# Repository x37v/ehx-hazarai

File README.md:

EHX stereo memory man with HAZARAI mod board
========

Kicad project, schematic and board

Inputs: beat/gate [filtered or unfiltered]
Outputs: loop, beat

Resources
---
* [Electro-Harmonix Stereo Memory Man with Hazarai](http://www.ehx.com/products/stereo-memory-man-with-hazarai) product page
* [dancerobotdance modified Stereo Memory Man with Hazarai](http://dancerobotdance.com/2011/05/modified-ehx-stereo-memory-man/) blog entry
* [navs.modular.lab More Hazarai! EHX SMMH Modification](http://navsmodularlab.blogspot.com/2009/08/more-hazarai-ehx-smmh-modification.html) blog entry
* [navs.modular.lab Even More Hazarai!](http://navsmodularlab.blogspot.com/2011/10/even-more-hazarai.html) blog entry
* [transistor cookbook](http://www.nutsvolts.com/magazine/article/bipolar_transistor_cookbook_part_3)

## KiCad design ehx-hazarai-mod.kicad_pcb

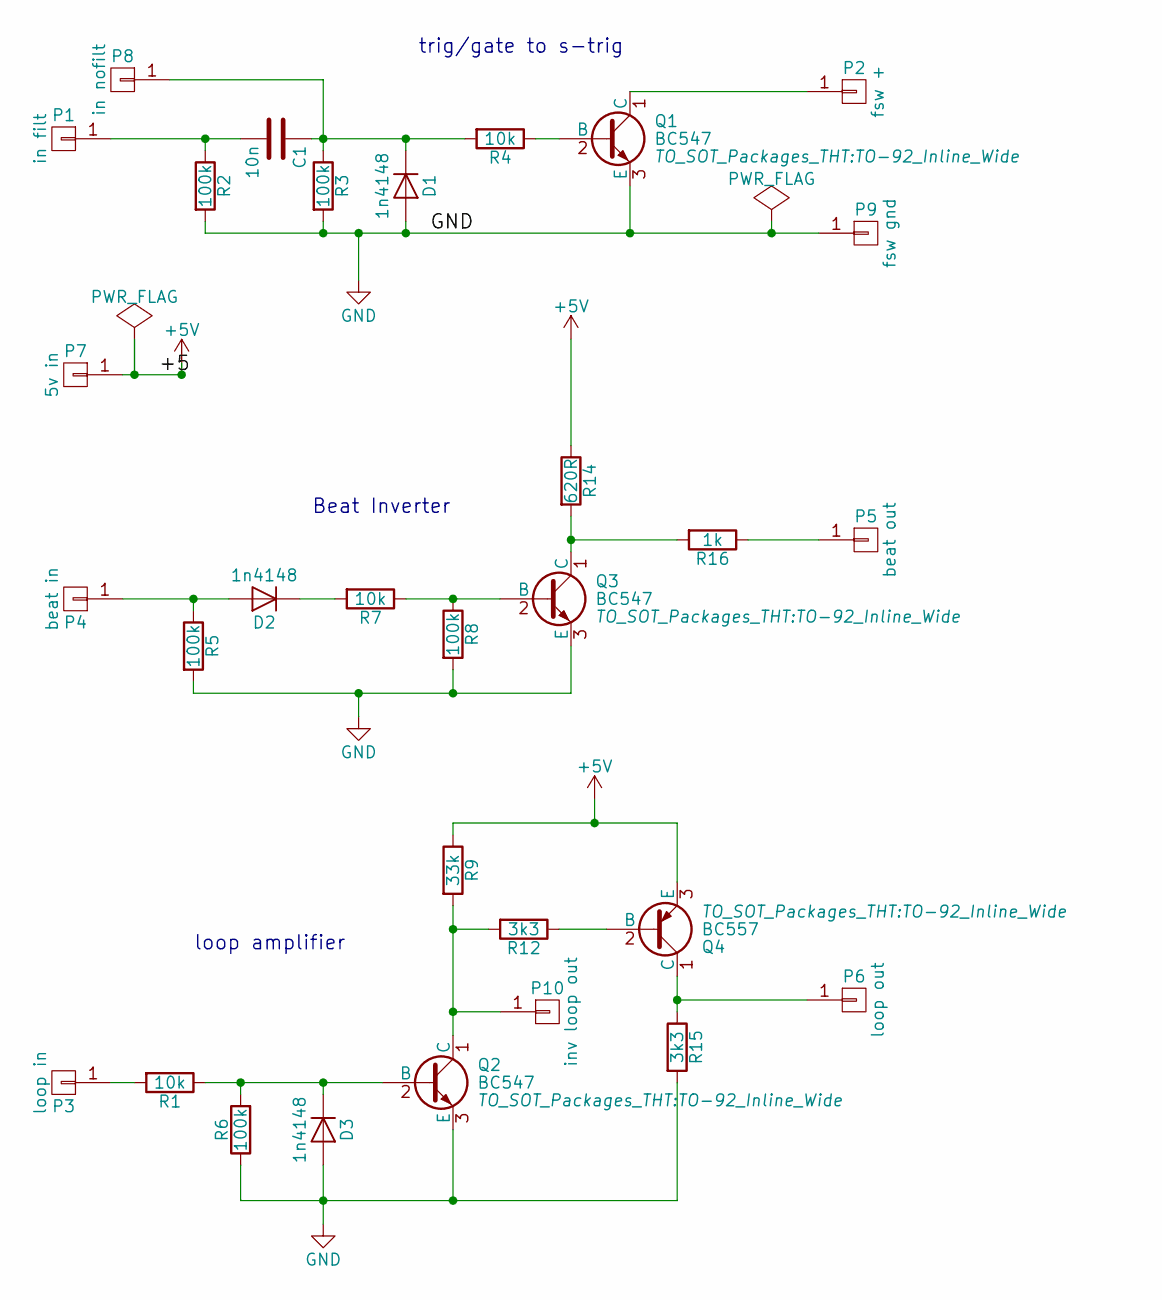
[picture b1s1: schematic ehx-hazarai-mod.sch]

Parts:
C1: 10n; C_Rect_L7_W4.5_P5
D1, D2, D3: 1n4148; Diode_DO-41_SOD81_Vertical_AnodeUp
P1: in filt; Pin_Header_Straight_1x01_Pitch2.54mm
P2: fsw +; Pin_Header_Straight_1x01_Pitch2.54mm
P3: loop in; Pin_Header_Straight_1x01_Pitch2.54mm
P4: beat in; Pin_Header_Straight_1x01_Pitch2.54mm
P5: beat out; Pin_Header_Straight_1x01_Pitch2.54mm
P6: loop out; Pin_Header_Straight_1x01_Pitch2.54mm
P7: 5v in; Pin_Header_Straight_1x01_Pitch2.54mm
P8: in nofilt; Pin_Header_Straight_1x01_Pitch2.54mm
P9: fsw gnd; Pin_Header_Straight_1x01_Pitch2.54mm
P10: inv loop out; Pin_Header_Straight_1x01_Pitch2.54mm
Q1, Q2, Q3: BC547; TO-92_Inline_Wide
Q4: BC557; TO-92_Inline_Wide
R1, R4, R7: 10k; Resistor_Vertical_RM5mm
R2, R3, R5, R6, R8: 100k; Resistor_Vertical_RM5mm
R9: 33k; Resistor_Vertical_RM5mm
R12, R15: 3k3; Resistor_Vertical_RM5mm
R14: 620R; Resistor_Vertical_RM5mm
R16: 1k; Resistor_Vertical_RM5mm

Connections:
+5V: P7.1, Q4.3 (E), R9.1, R14.1
GND: D1.2 (A), D3.2 (A), P9.1, Q1.3 (E), Q2.3 (E), Q3.3 (E), R2.2, R3.2, R5.2, R6.1, R8.2, R15.2
unnamed: C1.1, D1.1 (K), P8.1, R3.1, R4.2
unnamed: C1.2, P1.1, R2.1
unnamed: D2.1 (K), R7.2
unnamed: D2.2 (A), P4.1, R5.1
unnamed: D3.1 (K), Q2.2 (B), R1.1, R6.2
unnamed: P2.1, Q1.1 (C)
unnamed: P3.1, R1.2
unnamed: P5.1, R16.1
unnamed: P6.1, Q4.1 (C), R15.1
unnamed: P10.1, Q2.1 (C), R9.2, R12.2
unnamed: Q1.2 (B), R4.1
unnamed: Q3.1 (C), R14.2, R16.2
unnamed: Q3.2 (B), R7.1, R8.1
unnamed: Q4.2 (B), R12.1

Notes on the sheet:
Beat Inverter
trig/gate to s-trig
loop amplifier

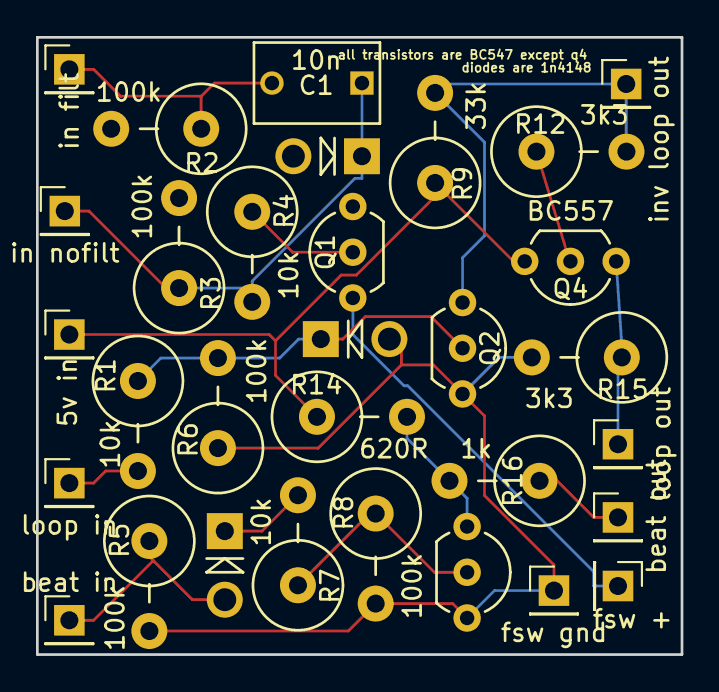
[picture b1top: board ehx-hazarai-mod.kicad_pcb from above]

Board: 2 copper layers, 35.8 x 34.3 mm, 31 parts (0 on the bottom side), 16 nets.

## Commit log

2017-04-01 fixed up ground
2017-04-01 updated connections and i/o.. should work now..
    needs a little more layout
2017-04-01 added readme
2017-04-01 added link to readme
2017-04-01 added more resources
